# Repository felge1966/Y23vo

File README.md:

# Y23vo
Neudesign des Mikrocomputers M.Kramer

Bisher sind folgende Baugruppen realisiert:
- CPU mit RAM und EPROM 
- BWS mit 2K Zeichengenerator 
- Floppycontroller mit u8272 (nach FA 07/1990)
- Grafikdisplaycontroller mit U82720 (nach FA 07/1990)
- 2PIO
- SIO mit U856, U857 und 8251
- Backplane mit 8 Steckplätzen

Alle Baugruppen können mit EFS 29 (A-B oder A-C) Steckverbindern oder alternativ mit DIN 41612 C 2*32 bestückt werden.

Bei CPU, 2PIO und SIO sind GALs als Decoder in Verwendung. 
Die Erstellung erfoolgte mit WinCUPL. Die Sourcen liegen im Verzeichnis

Die Verzeichnisse Redesign 2020 und Redesign 2022 stammen von der Nachetwicklung im Robotrontechnik-Forum.
-> ferrytale

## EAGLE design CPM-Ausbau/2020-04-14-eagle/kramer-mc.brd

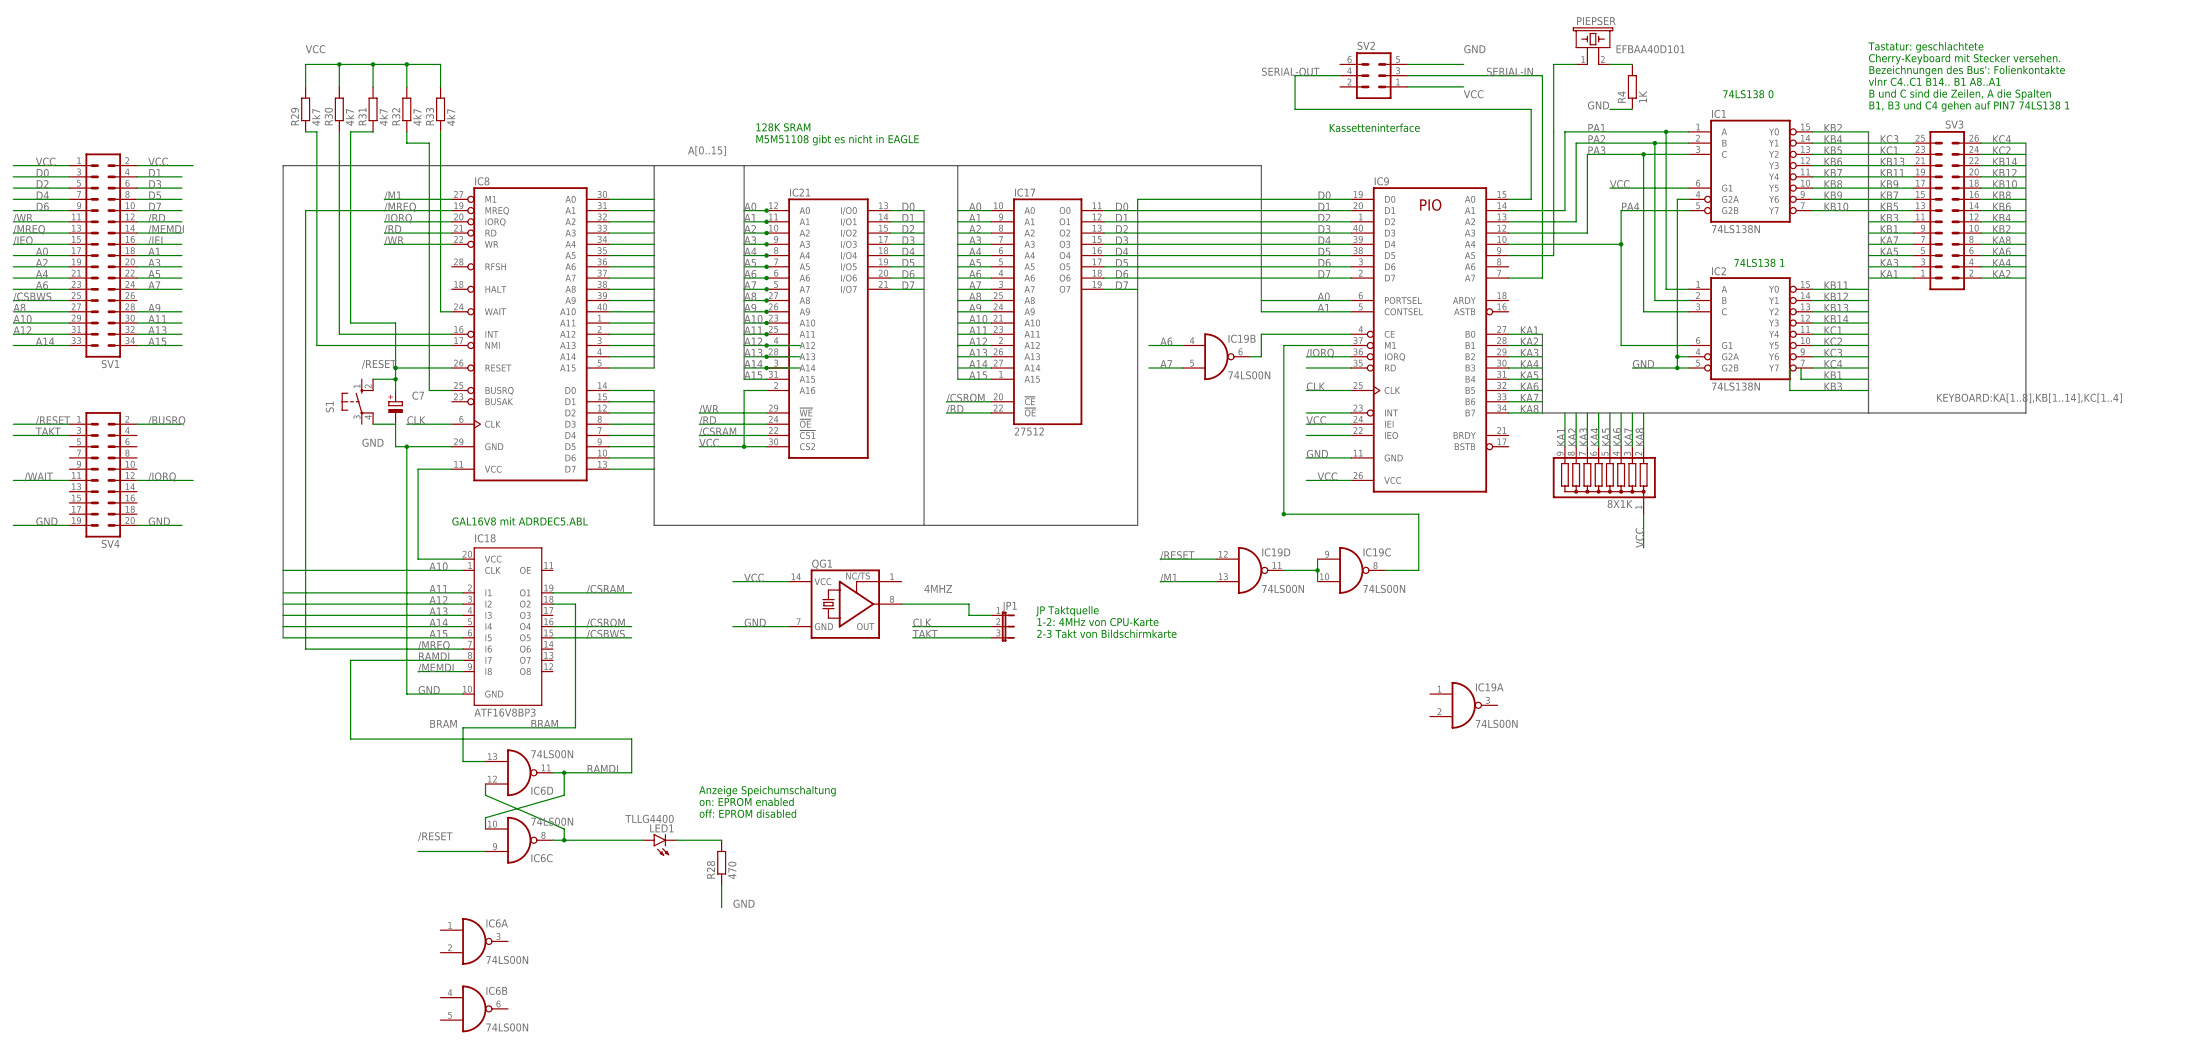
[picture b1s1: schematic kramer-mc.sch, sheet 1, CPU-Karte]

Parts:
8X1K: G08R; SIL9
C7: CPOL-EUE2-5; E2-5
IC1, IC2: 74LS138N; DIL16
IC6, IC19: 74LS00N; DIL14
IC8: Z80CPU; DIL40
IC9: Z80PIO; DIL40
IC17: 27512; DIL28
IC18: ATF16V8BP3; DIL20
IC21: LP621024CM; SOP32L
JP1: JP2E; JP2
LED1: TLLG4400; LED3MM
PIEPSER: EFBAA40D101
QG1: XO-14; DIL14S
R4: 1K; 0207/10
R28: 470; 0207/10
R29, R30, R31, R32, R33: 4k7; 0207/10
S1: 10-XX; B3F-10XX
SV1: ML34
SV2: ML6
SV3: ML26L
SV4: ML20

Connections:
4MHZ: JP1.1, QG1.8 (OUT)
/BUSRQ: SV4.2; also elsewhere on the board
/CSBWS: IC18.15 (O5), SV1.25; also elsewhere on the board
/CSRAM: IC18.19 (O1), IC21.22 (!CS1)
/CSROM: IC17.20 (!CE), IC18.16 (O4)
/IEI: SV1.16; also elsewhere on the board
/IEO: SV1.15; also elsewhere on the board
/IORQ: IC8.20 (IORQ), IC9.36 (IORQ), SV4.12; also elsewhere on the board
/M1: IC8.27 (M1), IC19.13 (I1); also elsewhere on the board
/MEMDI: IC18.9 (I8), SV1.14; also elsewhere on the board
/MREQ: IC8.19 (MREQ), IC18.7 (I6), SV1.13; also elsewhere on the board
/RD: IC8.21 (RD), IC17.22 (!OE), IC21.24 (!OE), SV1.12; also elsewhere on the board
/RESET: C7.+, IC6.9 (I0), IC8.26 (RESET), IC19.12 (I0), R31.1, S1.2 (S1), SV4.1; also elsewhere on the board
/WAIT: SV4.11; also elsewhere on the board
/WR: IC8.22 (WR), IC21.29 (!WE), SV1.11; also elsewhere on the board
A0: IC8.30 (A0), IC9.6 (PORTSEL), IC17.10 (A0), IC21.12 (A0), SV1.17; also elsewhere on the board
A1: IC8.31 (A1), IC9.5 (CONTSEL), IC17.9 (A1), IC21.11 (A1), SV1.18; also elsewhere on the board
A2: IC8.32 (A2), IC17.8 (A2), IC21.10 (A2), SV1.19; also elsewhere on the board
A3: IC8.33 (A3), IC17.7 (A3), IC21.9 (A3), SV1.20; also elsewhere on the board
A4: IC8.34 (A4), IC17.6 (A4), IC21.8 (A4), SV1.21; also elsewhere on the board
A5: IC8.35 (A5), IC17.5 (A5), IC21.7 (A5), SV1.22; also elsewhere on the board
A6: IC8.36 (A6), IC17.4 (A6), IC19.4 (I0), IC21.6 (A6), SV1.23; also elsewhere on the board
A7: IC8.37 (A7), IC17.3 (A7), IC19.5 (I1), IC21.5 (A7), SV1.24; also elsewhere on the board
A8: IC8.38 (A8), IC17.25 (A8), IC21.27 (A8), SV1.27; also elsewhere on the board
A9: IC8.39 (A9), IC17.24 (A9), IC21.26 (A9), SV1.28; also elsewhere on the board
A10: IC8.40 (A10), IC17.21 (A10), IC18.1 (CLK), IC21.23 (A10), SV1.29; also elsewhere on the board
A11: IC8.1 (A11), IC17.23 (A11), IC18.2 (I1), IC21.25 (A11), SV1.30; also elsewhere on the board
A12: IC8.2 (A12), IC17.2 (A12), IC18.3 (I2), IC21.4 (A12), SV1.31; also elsewhere on the board
A13: IC8.3 (A13), IC17.26 (A13), IC18.4 (I3), IC21.28 (A13), SV1.32; also elsewhere on the board
A14: IC8.4 (A14), IC17.27 (A14), IC18.5 (I4), IC21.3 (A14), SV1.33; also elsewhere on the board
A15: IC8.5 (A15), IC17.1 (A15), IC18.6 (I5), IC21.31 (A15), SV1.34; also elsewhere on the board
BRAM: IC6.13 (I1), IC18.18 (O2)
CLK: IC8.6 (CLK), IC9.25 (CLK), JP1.2
D0: IC8.14 (D0), IC9.19 (D0), IC17.11 (O0), IC21.13 (I/O0), SV1.3; also elsewhere on the board
D1: IC8.15 (D1), IC9.20 (D1), IC17.12 (O1), IC21.14 (I/O1), SV1.4; also elsewhere on the board
D2: IC8.12 (D2), IC9.1 (D2), IC17.13 (O2), IC21.15 (I/O2), SV1.5; also elsewhere on the board
D3: IC8.8 (D3), IC9.40 (D3), IC17.15 (O3), IC21.17 (I/O3), SV1.6; also elsewhere on the board
D4: IC8.7 (D4), IC9.39 (D4), IC17.16 (O4), IC21.18 (I/O4), SV1.7; also elsewhere on the board
D5: IC8.9 (D5), IC9.38 (D5), IC17.17 (O5), IC21.19 (I/O5), SV1.8; also elsewhere on the board
D6: IC8.10 (D6), IC9.3 (D6), IC17.18 (O6), IC21.20 (I/O6), SV1.9; also elsewhere on the board
D7: IC8.13 (D7), IC9.2 (D7), IC17.19 (O7), IC21.21 (I/O7), SV1.10; also elsewhere on the board
GND: C7.-, IC1.4 (G2A), IC1.8 (GND), IC2.4 (G2A), IC2.5 (G2B), IC2.8 (GND), IC6.7 (GND), IC8.29 (GND), IC9.11 (GND), IC17.14 (GND), IC18.10 (GND), IC19.7 (GND), IC21.16 (GND), QG1.7 (GND), R4.1, R28.1, S1.4 (P1), SV2.5, SV4.19, SV4.20; also elsewhere on the board
KA1: 8X1K.9, IC9.27 (B0), SV3.1
KA2: 8X1K.8, IC9.28 (B1), SV3.2
KA3: 8X1K.7, IC9.29 (B2), SV3.3
KA4: 8X1K.6, IC9.30 (B3), SV3.4
KA5: 8X1K.5, IC9.31 (B4), SV3.5
KA6: 8X1K.4, IC9.32 (B5), SV3.6
KA7: 8X1K.3, IC9.33 (B6), SV3.7
KA8: 8X1K.2, IC9.34 (B7), SV3.8
KB1: SV3.9
KB2: IC1.15 (Y0), SV3.10
KB3: SV3.11
KB4: IC1.14 (Y1), SV3.12
KB5: IC1.13 (Y2), SV3.13
KB6: IC1.12 (Y3), SV3.14
KB7: IC1.11 (Y4), SV3.15
KB8: IC1.10 (Y5), SV3.16
KB9: IC1.9 (Y6), SV3.17
KB10: IC1.7 (Y7), SV3.18
KB11: IC2.15 (Y0), SV3.19
KB12: IC2.14 (Y1), SV3.20
KB13: IC2.13 (Y2), SV3.21
KB14: IC2.12 (Y3), SV3.22
KC1: IC2.11 (Y4), SV3.23
KC2: IC2.10 (Y5), SV3.24
KC3: IC2.9 (Y6), SV3.25
KC4: IC2.7 (Y7), SV3.26
unnamed: IC19.9 (I0), IC19.10 (I1), IC19.11 (O)
unnamed: IC8.11 (VCC), IC18.20 (VCC)
unnamed: IC6.8 (O), IC6.12 (I0), LED1.A
unnamed: LED1.K (C), R28.2
unnamed: IC9.9 (A5), PIEPSER.1
unnamed: PIEPSER.2, R4.2
unnamed: IC9.4 (CE), IC19.6 (O)
unnamed: IC9.37 (M1), IC19.8 (O)
unnamed: IC8.17 (NMI), R29.1
unnamed: IC8.16 (INT), R30.1
unnamed: IC8.24 (WAIT), R33.1
unnamed: IC8.25 (BUSRQ), R32.1
PA1: IC1.1 (A), IC2.1 (A), IC9.14 (A1)
PA2: IC1.2 (B), IC2.2 (B), IC9.13 (A2)
PA3: IC1.3 (C), IC2.3 (C), IC9.12 (A3)
PA4: IC1.5 (G2B), IC2.6 (G1), IC9.10 (A4)
RAMDI: IC6.10 (I1), IC6.11 (O), IC18.8 (I7)
SERIAL-IN: IC9.7 (A7), SV2.3
SERIAL-OUT: IC9.15 (A0), SV2.4
TAKT: JP1.3, SV4.3; also elsewhere on the board
VCC: 8X1K.1, IC1.6 (G1), IC1.16 (VCC), IC2.16 (VCC), IC6.14 (VCC), IC9.24 (IEI), IC9.26 (VCC), IC17.28 (VCC), IC19.14 (VCC), IC21.2 (A16), IC21.30 (CS2), IC21.32 (VCC), QG1.14 (VCC), R29.2, R30.2, R31.2, R32.2, R33.2, SV1.1, SV1.2, SV2.1; also elsewhere on the board

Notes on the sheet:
GAL16V8 mit ADRDEC5.ABL
Tastatur: geschlachtete Cherry-Keyboard mit Stecker versehen. Bezeichnungen des Bus': Folienkontakte vlnr C4..C1 B14.. B1 A8..A1 B und C sind die Zeilen, A die Spalten B1, B3 und C4 gehen auf PIN7 74LS138 1
74LS138 1
74LS138 0
Kassetteninterface
128K SRAM M5M51108 gibt es nicht in EAGLE
Anzeige Speichumschaltung on: EPROM enabled off: EPROM disabled
JP Taktquelle 1-2: 4MHz von CPU-Karte 2-3 Takt von Bildschirmkarte

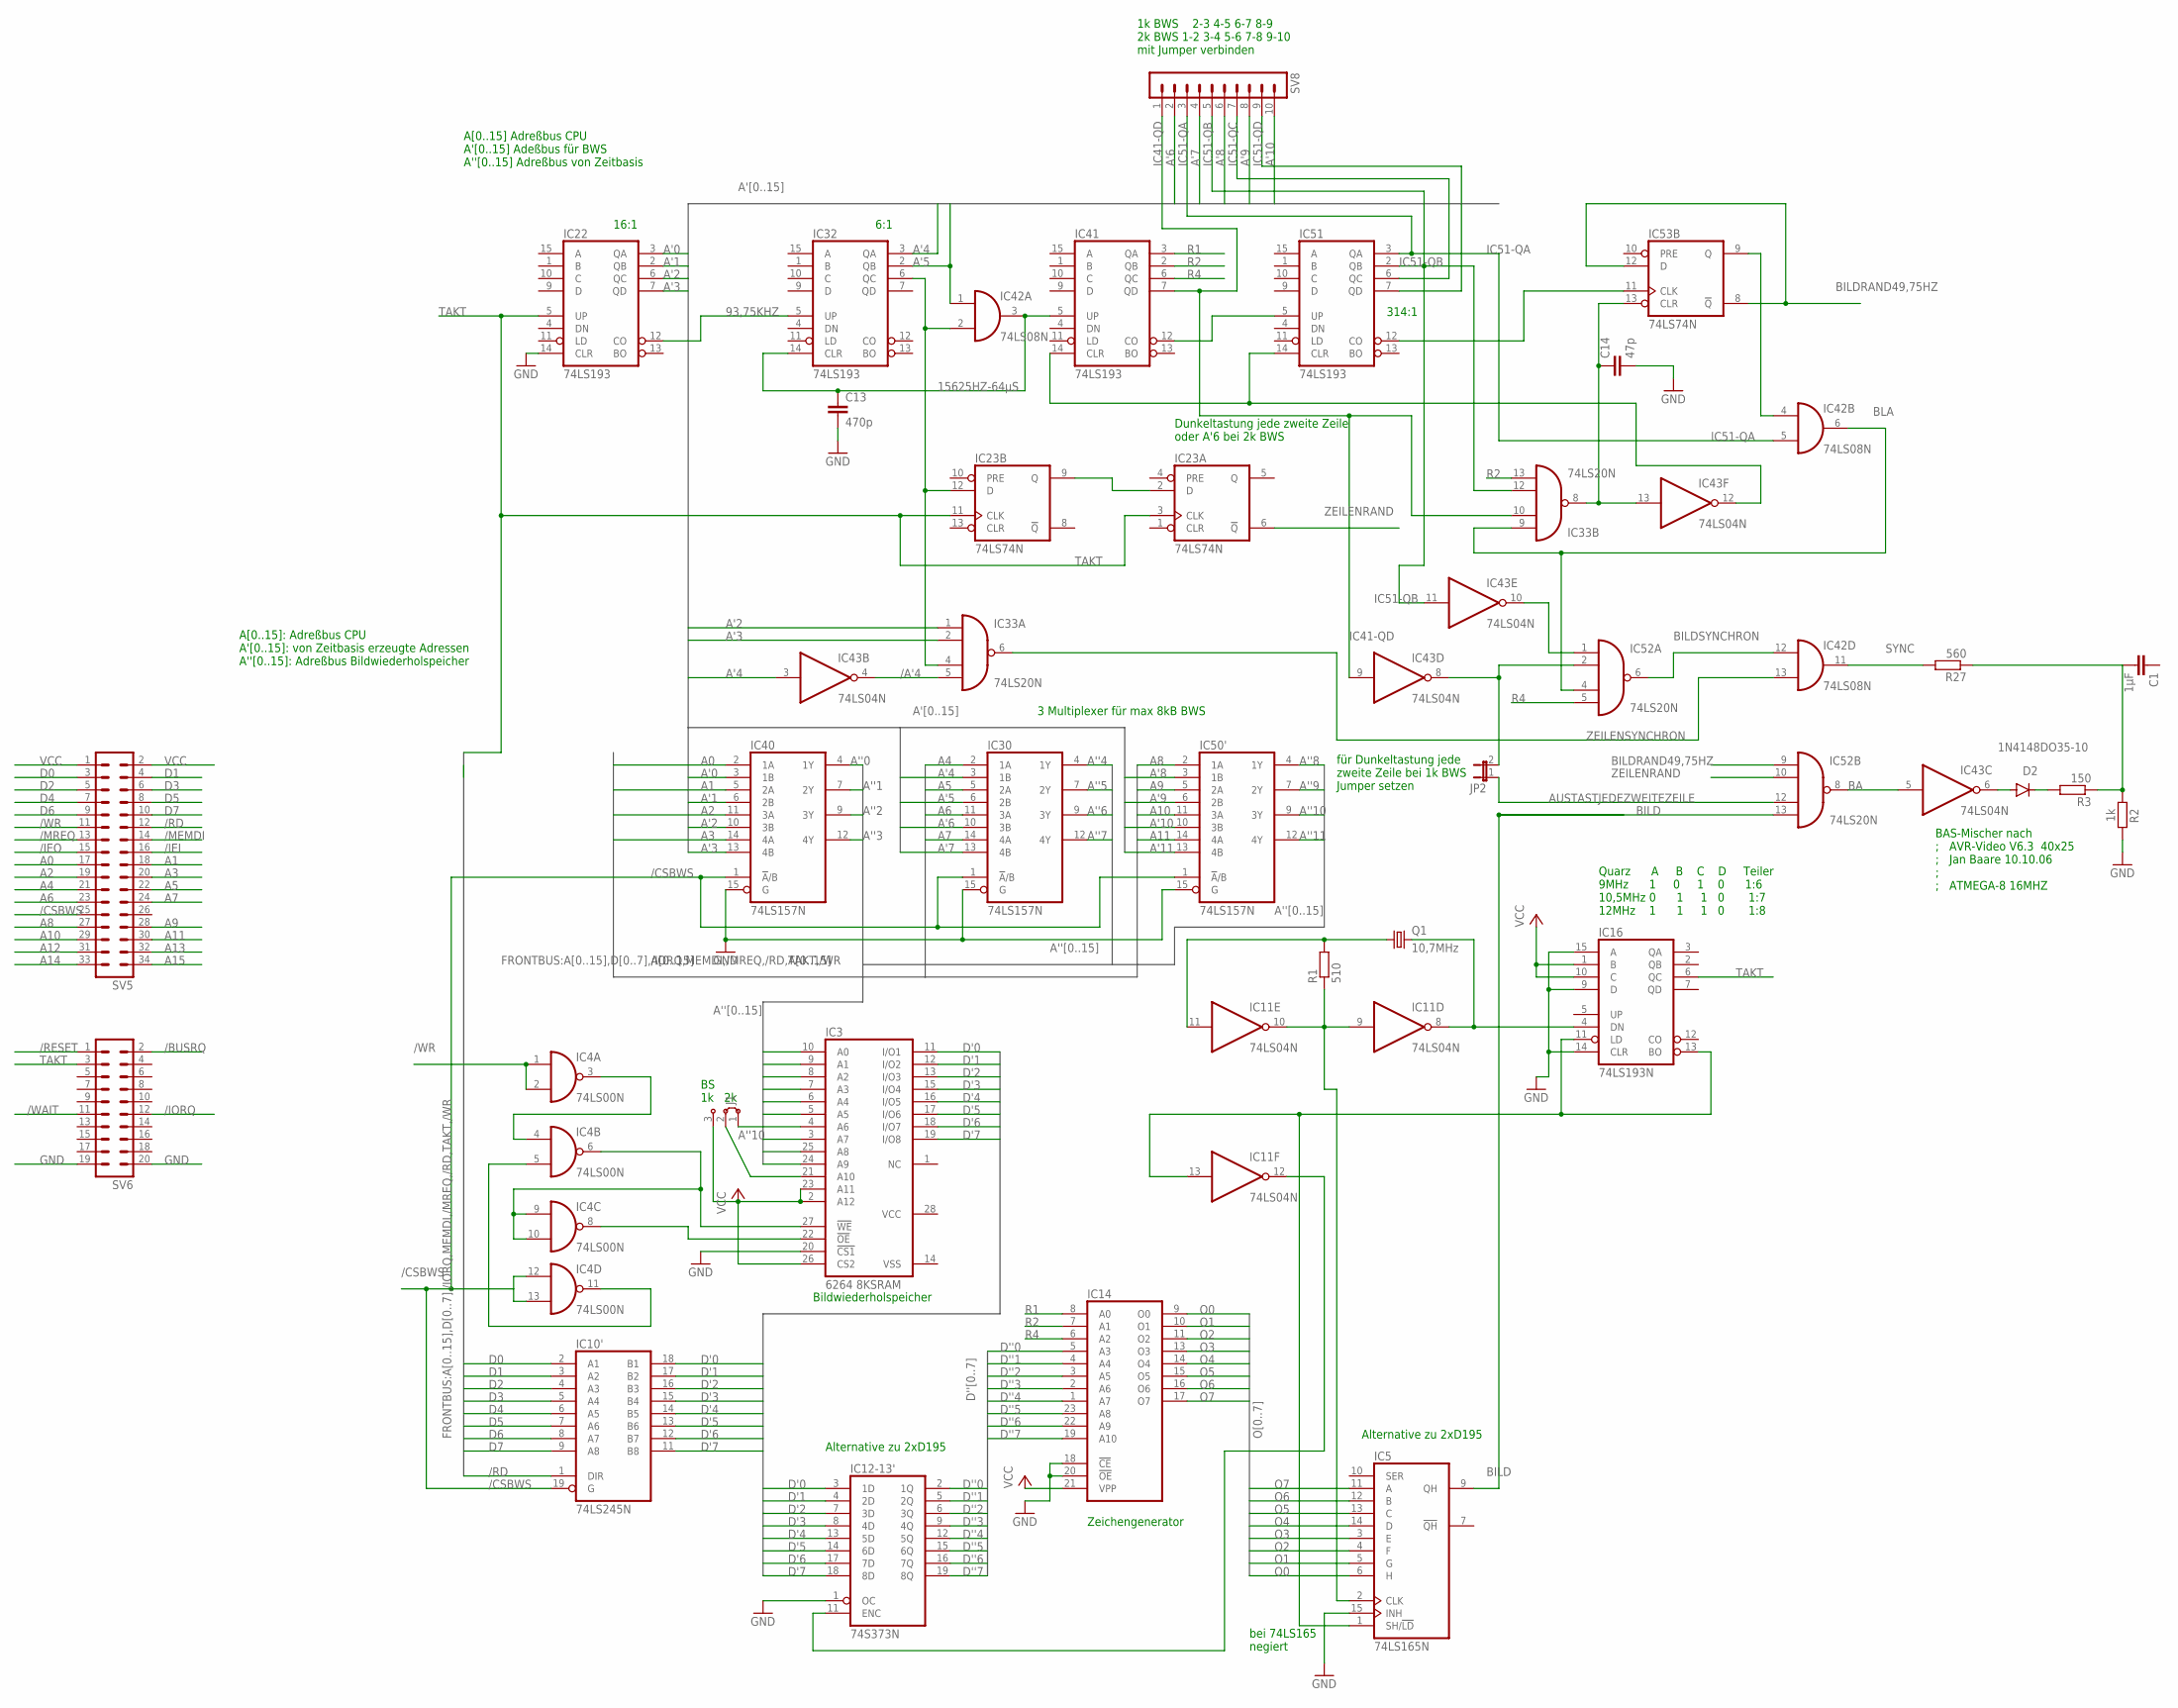
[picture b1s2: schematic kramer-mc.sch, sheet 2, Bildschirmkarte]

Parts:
C1: 1µF; C050-025X075
C13: 470p; C050-024X044
C14: 47p; C050-024X044
D2: 1N4148DO35-10; DO35-10
IC3: 6264 8KSRAM; DIL28-6
IC4: 74LS00N; DIL14
IC5: 74LS165N; DIL16
IC10': 74LS245N; DIL20
IC11, IC43: 74LS04N; DIL14
IC12-13': 74S373N; DIL20
IC14: 2716; DIL24
IC16: 74LS193N; DIL16
IC22, IC32, IC41, IC51: 74LS193; DIL16
IC23, IC53: 74LS74N; DIL14
IC30, IC40, IC50': 74LS157N; DIL16
IC33, IC52: 74LS20N; DIL14
IC42: 74LS08N; DIL14
J1: J2X2MM; 04C
JP2: JP1E; JP1
Q1: 10,7MHz; HC49U-V
R1: 510; 0309/12
R2: 1k; 0309/12
R3: 150; 0309/12
R27: 560; 0309/12
SV5: ML34
SV6: ML20
SV8: MA10-1

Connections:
93,75KHZ: IC22.12 (CO), IC32.5 (UP)
15625HZ-64µS: C13.1, IC32.14 (CLR), IC41.5 (UP), IC42.3 (O)
/A'4: IC33.5 (I3), IC43.4 (O)
/BUSRQ: SV6.2; also elsewhere on the board
/CSBWS: IC4.12 (I0), IC4.13 (I1), IC10'.19 (G), IC30.1 (!A!/B), IC40.1 (!A!/B), IC50'.1 (!A!/B), SV5.25; also elsewhere on the board
/IEI: SV5.16; also elsewhere on the board
/IEO: SV5.15; also elsewhere on the board
/IORQ: SV6.12; also elsewhere on the board
/MEMDI: SV5.14; also elsewhere on the board
/MREQ: SV5.13; also elsewhere on the board
/RD: IC10'.1 (DIR), SV5.12; also elsewhere on the board
/RESET: SV6.1; also elsewhere on the board
/WAIT: SV6.11; also elsewhere on the board
/WR: IC4.1 (I0), IC4.2 (I1), SV5.11; also elsewhere on the board
A0: IC40.2 (1A), SV5.17; also elsewhere on the board
A1: IC40.5 (2A), SV5.18; also elsewhere on the board
A2: IC40.11 (3A), SV5.19; also elsewhere on the board
A3: IC40.14 (4A), SV5.20; also elsewhere on the board
A4: IC30.2 (1A), SV5.21; also elsewhere on the board
A5: IC30.5 (2A), SV5.22; also elsewhere on the board
A6: IC30.11 (3A), SV5.23; also elsewhere on the board
A7: IC30.14 (4A), SV5.24; also elsewhere on the board
A8: IC50'.2 (1A), SV5.27; also elsewhere on the board
A9: IC50'.5 (2A), SV5.28; also elsewhere on the board
A10: IC50'.11 (3A), SV5.29; also elsewhere on the board
A11: IC50'.14 (4A), SV5.30; also elsewhere on the board
A12: SV5.31; also elsewhere on the board
A13: SV5.32; also elsewhere on the board
A14: SV5.33; also elsewhere on the board
A15: SV5.34; also elsewhere on the board
A'0: IC22.3 (QA), IC40.3 (1B)
A'1: IC22.2 (QB), IC40.6 (2B)
A'2: IC22.6 (QC), IC33.1 (I0), IC40.10 (3B)
A'3: IC22.7 (QD), IC33.2 (I1), IC40.13 (4B)
A'4: IC30.3 (1B), IC32.3 (QA), IC43.3 (I)
A'5: IC30.6 (2B), IC32.2 (QB), IC42.1 (I0)
A'6: IC30.10 (3B), SV8.2
A'7: IC30.13 (4B), SV8.4
A'8: IC50'.3 (1B), SV8.6
A'9: IC50'.6 (2B), SV8.8
A'10: IC50'.10 (3B), SV8.10
A'11: IC50'.13 (4B)
A''0: IC3.10 (A0), IC40.4 (1Y)
A''1: IC3.9 (A1), IC40.7 (2Y)
A''2: IC3.8 (A2), IC40.9 (3Y)
A''3: IC3.7 (A3), IC40.12 (4Y)
A''4: IC3.6 (A4), IC30.4 (1Y)
A''5: IC3.5 (A5), IC30.7 (2Y)
A''6: IC3.4 (A6), IC30.9 (3Y)
A''7: IC3.3 (A7), IC30.12 (4Y)
A''8: IC3.25 (A8), IC50'.4 (1Y)
A''9: IC3.24 (A9), IC50'.7 (2Y)
A''10: IC50'.9 (3Y), J1.1
A''11: IC50'.12 (4Y)
AUSTASTJEDEZWEITEZEILE: IC52.12 (I2), JP2.1
BA: IC43.5 (I), IC52.8 (O)
BILD: IC5.9 (QH), IC52.13 (I3)
BILDRAND49,75HZ: IC52.9 (I0), IC53.8 (!Q), IC53.12 (D)
BILDSYNCHRON: IC42.12 (I0), IC52.6 (O)
BLA: IC33.9 (I0), IC42.6 (O), IC52.4 (I2)
D0: IC10'.2 (A1), SV5.3; also elsewhere on the board
D1: IC10'.3 (A2), SV5.4; also elsewhere on the board
D2: IC10'.4 (A3), SV5.5; also elsewhere on the board
D3: IC10'.5 (A4), SV5.6; also elsewhere on the board
D4: IC10'.6 (A5), SV5.7; also elsewhere on the board
D5: IC10'.7 (A6), SV5.8; also elsewhere on the board
D6: IC10'.8 (A7), SV5.9; also elsewhere on the board
D7: IC10'.9 (A8), SV5.10; also elsewhere on the board
D'0: IC3.11 (I/O1), IC10'.18 (B1), IC12-13'.3 (1D)
D'1: IC3.12 (I/O2), IC10'.17 (B2), IC12-13'.4 (2D)
D'2: IC3.13 (I/O3), IC10'.16 (B3), IC12-13'.7 (3D)
D'3: IC3.15 (I/O4), IC10'.15 (B4), IC12-13'.8 (4D)
D'4: IC3.16 (I/O5), IC10'.14 (B5), IC12-13'.13 (5D)
D'5: IC3.17 (I/O6), IC10'.13 (B6), IC12-13'.14 (6D)
D'6: IC3.18 (I/O7), IC10'.12 (B7), IC12-13'.17 (7D)
D'7: IC3.19 (I/O8), IC10'.11 (B8), IC12-13'.18 (8D)
D''0: IC12-13'.2 (1Q), IC14.5 (A3)
D''1: IC12-13'.5 (2Q), IC14.4 (A4)
D''2: IC12-13'.6 (3Q), IC14.3 (A5)
D''3: IC12-13'.9 (4Q), IC14.2 (A6)
D''4: IC12-13'.12 (5Q), IC14.1 (A7)
D''5: IC12-13'.15 (6Q), IC14.23 (A8)
D''6: IC12-13'.16 (7Q), IC14.22 (A9)
D''7: IC12-13'.19 (8Q), IC14.19 (A10)
GND: C13.2, C14.2, IC3.20 (!CS1), IC4.7 (GND), IC5.8 (GND), IC5.15 (INH), IC10'.10 (GND), IC11.7 (GND), IC12-13'.1 (OC), IC12-13'.10 (GND), IC14.12 (GND), IC14.18 (!CE), IC14.20 (!OE), IC16.8 (GND), IC16.9 (D), IC16.14 (CLR), IC16.15 (A), IC22.8 (GND), IC22.14 (CLR), IC23.7 (GND), IC30.8 (GND), IC30.15 (G), IC32.8 (GND), IC33.7 (GND), IC40.8 (GND), IC40.15 (G), IC41.8 (GND), IC42.7 (GND), IC43.7 (GND), IC50'.8 (GND), IC50'.15 (G), IC51.8 (GND), IC52.7 (GND), IC53.7 (GND), R2.2, SV6.19, SV6.20; also elsewhere on the board
IC41-QD: IC33.10 (I1), IC41.7 (QD), IC43.9 (I), SV8.1
IC51-QA: IC42.5 (I1), IC51.3 (QA), SV8.3
IC51-QB: IC33.12 (I2), IC43.11 (I), IC51.2 (QB), SV8.5
IC51-QC: IC51.6 (QC), SV8.7
IC51-QD: IC51.7 (QD), SV8.9
unnamed: IC43.8 (O), IC52.2 (I1), JP2.2
unnamed: IC41.12 (CO), IC51.5 (UP)
unnamed: IC23.12 (D), IC32.6 (QC), IC33.4 (I2), IC42.2 (I1)
unnamed: IC23.2 (D), IC23.9 (Q)
unnamed: IC41.14 (CLR), IC43.12 (O), IC51.14 (CLR)
unnamed: IC51.12 (CO), IC53.11 (CLK)
unnamed: IC3.21 (A10), J1.2
unnamed: IC42.4 (I0), IC53.9 (Q)
unnamed: IC4.3 (O), IC4.4 (I0)
unnamed: C14.1, IC33.8 (O), IC43.13 (I), IC53.13 (CLR)
unnamed: IC43.10 (O), IC52.1 (I0)
unnamed: IC5.2 (CLK), IC11.9 (I), IC11.10 (O), R1.1
unnamed: IC11.12 (O), IC12-13'.11 (ENC)
unnamed: D2.A, IC43.6 (O)
unnamed: IC11.8 (O), IC16.4 (DN), Q1.2
unnamed: IC11.11 (I), Q1.1, R1.2
unnamed: IC5.1 (SH/!LD), IC11.13 (I), IC16.11 (LD), IC16.13 (BO)
unnamed: D2.C, R3.2
unnamed: C1.2, R2.1, R3.1, R27.1
unnamed: IC4.5 (I1), IC4.11 (O)
unnamed: IC3.22 (!OE), IC4.8 (O)
unnamed: IC3.27 (!WE), IC4.6 (O), IC4.9 (I0), IC4.10 (I1)
O0: IC5.6 (H), IC14.9 (O0)
O1: IC5.5 (G), IC14.10 (O1)
O2: IC5.4 (F), IC14.11 (O2)
O3: IC5.3 (E), IC14.13 (O3)
O4: IC5.14 (D), IC14.14 (O4)
O5: IC5.13 (C), IC14.15 (O5)
O6: IC5.12 (B), IC14.16 (O6)
O7: IC5.11 (A), IC14.17 (O7)
R1: IC14.8 (A0), IC41.3 (QA)
R2: IC14.7 (A1), IC33.13 (I3), IC41.2 (QB)
R4: IC14.6 (A2), IC41.6 (QC), IC52.5 (I3)
SYNC: IC42.11 (O), R27.2
TAKT: IC16.6 (QC), IC22.5 (UP), IC23.3 (CLK), IC23.11 (CLK), SV6.3; also elsewhere on the board
VCC: IC3.2 (A12), IC3.23 (A11), IC3.26 (CS2), IC3.28 (VCC), IC4.14 (VCC), IC5.16 (VCC), IC10'.20 (VCC), IC11.14 (VCC), IC12-13'.20 (VCC), IC14.21 (VPP), IC14.24 (VCC), IC16.1 (B), IC16.10 (C), IC16.16 (VCC), IC22.16 (VCC), IC23.14 (VCC), IC30.16 (VCC), IC32.16 (VCC), IC33.14 (VCC), IC40.16 (VCC), IC41.16 (VCC), IC42.14 (VCC), IC43.14 (VCC), IC50'.16 (VCC), IC51.16 (VCC), IC52.14 (VCC), IC53.14 (VCC), J1.3, SV5.1, SV5.2; also elsewhere on the board
VSS: IC3.14 (VSS)
ZEILENRAND: IC23.6 (!Q), IC52.10 (I1)
ZEILENSYNCHRON: IC33.6 (O), IC42.13 (I1)

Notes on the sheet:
Alternative zu 2xD195
bei 74LS165 negiert
A[0..15] Adreßbus CPU A'[0..15] Adeßbus für BWS A''[0..15] Adreßbus von Zeitbasis
Bildwiederholspeicher
Zeichengenerator
3 Multiplexer für max 8kB BWS
Quarz A B C D Teiler 9MHz 1 0 1 0 1:6 10,5MHz 0 1 1 0 1:7 12MHz 1 1 1 0 1:8
BAS-Mischer nach ; AVR-Video V6.3 40x25 ; Jan Baare 10.10.06 ; ; ATMEGA-8 16MHZ
A[0..15]: Adreßbus CPU A'[0..15]: von Zeitbasis erzeugte Adressen A''[0..15]: Adreßbus Bildwiederholspeicher
Dunkeltastung jede zweite Zeile oder A'6 bei 2k BWS
16:1
6:1
für Dunkeltastung jede zweite Zeile bei 1k BWS Jumper setzen
BS 1k 2k
1k BWS 2-3 4-5 6-7 8-9 2k BWS 1-2 3-4 5-6 7-8 9-10 mit Jumper verbinden
314:1

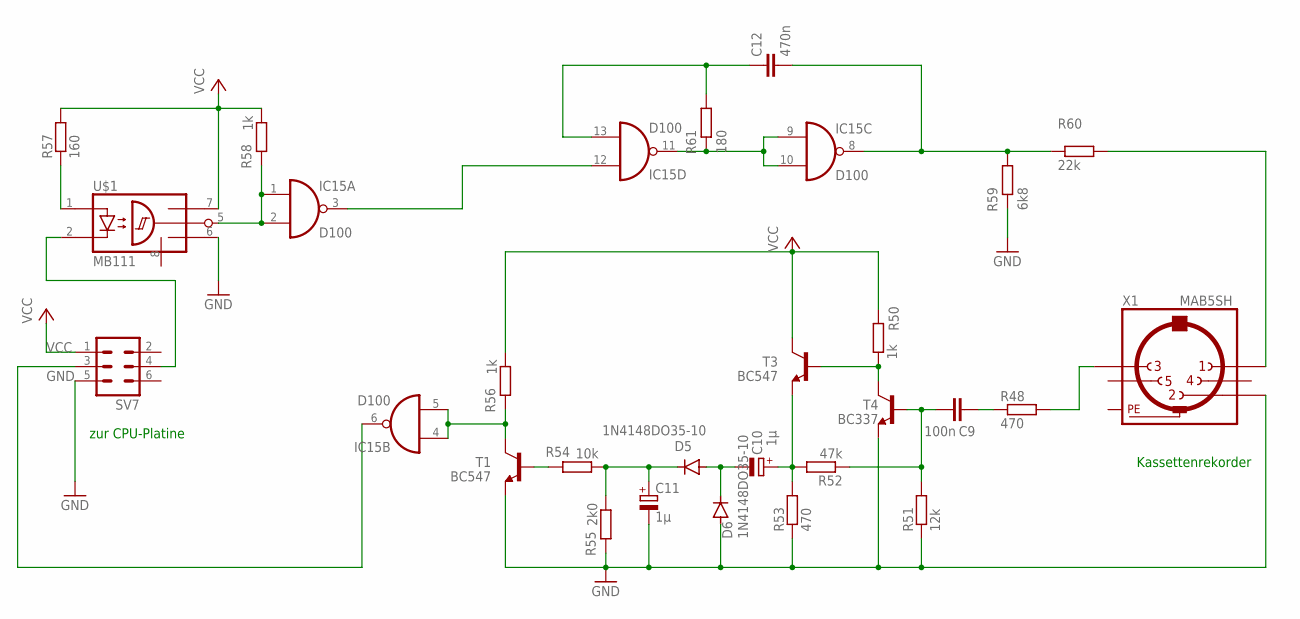
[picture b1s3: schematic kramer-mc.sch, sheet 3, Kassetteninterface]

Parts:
C9: 100n; C025-025X050
C10, C11: 1µ; E2,5-6E
C12: 470n; C150-064X183
D5, D6: 1N4148DO35-10; DO35-10
IC15: D100; DIL14
R48, R53: 470; 0207/10
R50, R56, R58: 1k; 0207/10
R51: 12k; 0207/10
R52: 47k; 0207/10
R54: 10k; 0207/10
R55: 2k0; 0207/10
R57: 160; 0207/10
R59: 6k8; 0207/10
R60: 22k; 0207/10
R61: 180; 0207/10
SV7: ML6
T1, T3: BC547; TO92
T4: BC337; TO92
U$1: MB111; DIL8
X1: MAB5SH

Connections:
GND: C11.-, D6.A, IC15.7 (GND), R51.1, R53.1, R55.2, R59.2, SV7.5, T1.1 (E), T4.1 (E), U$1.6 (GND1), X1.2; also elsewhere on the board
unnamed: IC15.6 (O), SV7.3
unnamed: SV7.4, U$1.2 (C)
unnamed: R48.2, X1.3
unnamed: C9.1, R48.1
unnamed: C9.2, R51.2, R52.1, T4.2 (B)
unnamed: R50.1, T3.2 (B), T4.3 (C)
unnamed: R57.1, U$1.1 (A)
unnamed: C10.+, R52.2, R53.2, T3.1 (E)
unnamed: IC15.1 (I0), IC15.2 (I1), R58.2, U$1.5 (OUT1)
unnamed: C10.-, D5.A, D6.C
unnamed: C11.+, D5.C, R54.1, R55.1
unnamed: R60.2, X1.1
unnamed: R54.2, T1.2 (B)
unnamed: IC15.4 (I0), IC15.5 (I1), R56.2, T1.3 (C)
unnamed: IC15.9 (I0), IC15.10 (I1), IC15.11 (O), R61.2
unnamed: C12.1, IC15.13 (I1), R61.1
unnamed: C12.2, IC15.8 (O), R59.1, R60.1
unnamed: IC15.3 (O), IC15.12 (I0)
PE: X1.PE, X1.PE@ (PE)
VCC: IC15.14 (VCC), R50.2, R56.1, R57.2, R58.1, SV7.1, T3.3 (C), U$1.7 (VCC1); also elsewhere on the board

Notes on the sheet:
zur CPU-Platine
Kassettenrekorder

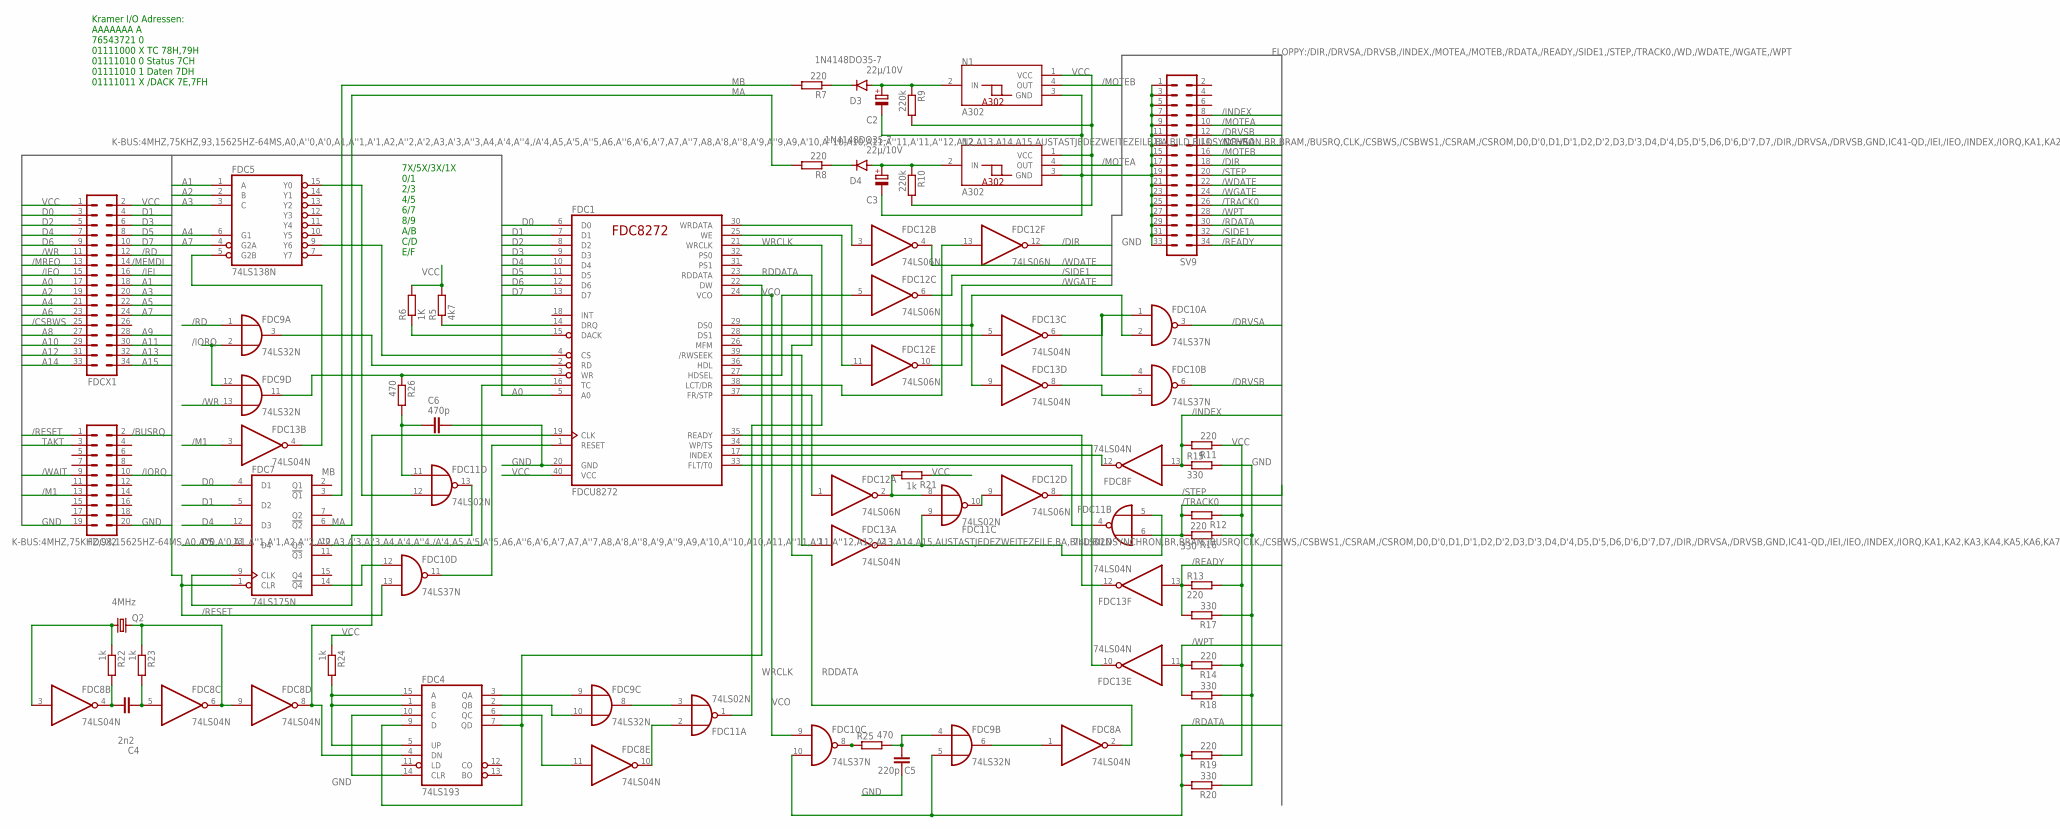
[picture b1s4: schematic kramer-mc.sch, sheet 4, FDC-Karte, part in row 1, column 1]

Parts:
C2, C3: 22µ/10V; E2,5-5
C4: 2n2; C025-025X050
C5: 220p; C025-025X050
C6: 470p; C025-025X050
D3, D4: 1N4148DO35-7; DO35-7
FDC1: FDCU8272; DIL40
FDC4: 74LS193; DIL16
FDC5: 74LS138N; DIL16
FDC7: 74LS175N; DIL16
FDC8, FDC13: 74LS04N; DIL14
FDC9: 74LS32N; DIL14
FDC10: 74LS37N; DIL14
FDC11: 74LS02N; DIL14
FDC12: 74LS06N; DIL14
FDCX1: ML34
FDCX2: ML20
N1, N2: A302; DIL04
Q2: 4MHz; HC49U-V
R5: 4k7; 0207/10
R6: 1K; 0207/10
R7, R8, R11, R12, R13, R14, R19: 220; 0207/10
R9, R10: 220k; 0207/10
R15, R16, R17, R18, R20: 330; 0207/10
R21, R22, R23, R24: 1k; 0207/10
R25, R26: 470; 0207/10
SV9: ML34

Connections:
/BUSRQ: FDCX2.2; also elsewhere on the board
/CSBWS: FDCX1.25; also elsewhere on the board
/DIR: FDC12.12 (O), SV9.18
/DRVSA: FDC10.3 (O), SV9.14
/DRVSB: FDC10.6 (O), SV9.12
/IEI: FDCX1.16; also elsewhere on the board
/IEO: FDCX1.15; also elsewhere on the board
/INDEX: FDC8.13 (I), R11.2, R15.1, SV9.8
/IORQ: FDC9.2 (I1), FDC9.12 (I0), FDCX2.10; also elsewhere on the board
/M1: FDC13.3 (I), FDCX2.13; also elsewhere on the board
/MEMDI: FDCX1.14; also elsewhere on the board
/MOTEA: N2.4 (OUT), SV9.10
/MOTEB: N1.4 (OUT), SV9.16
/MREQ: FDCX1.13; also elsewhere on the board
/RD: FDC9.1 (I0), FDCX1.12; also elsewhere on the board
/RDATA: FDC9.5 (I1), FDC10.10 (I1), R19.2, R20.2, SV9.30
/READY: FDC13.13 (I), R13.1, R17.2, SV9.34
/RESET: FDC7.1 (CLR), FDC10.13 (I1), FDCX2.1; also elsewhere on the board
/SIDE1: FDC12.6 (O), SV9.32
/STEP: FDC12.8 (O), SV9.20
/TRACK0: FDC11.6 (I1), R12.2, R16.2, SV9.26
/WAIT: FDCX2.9; also elsewhere on the board
/WDATE: FDC12.4 (O), SV9.22
/WGATE: FDC12.10 (O), SV9.24
/WPT: FDC13.11 (I), R14.2, R18.2, SV9.28
/WR: FDC9.13 (I1), FDCX1.11; also elsewhere on the board
A0: FDC1.5 (A0), FDCX1.17; also elsewhere on the board
A1: FDC5.1 (A), FDCX1.18; also elsewhere on the board
A2: FDC5.2 (B), FDCX1.19; also elsewhere on the board
A3: FDC5.3 (C), FDCX1.20; also elsewhere on the board
A4: FDC5.6 (G1), FDCX1.21; also elsewhere on the board
A5: FDCX1.22; also elsewhere on the board
A6: FDCX1.23; also elsewhere on the board
A7: FDC5.4 (G2A), FDCX1.24; also elsewhere on the board
A8: FDCX1.27; also elsewhere on the board
A9: FDCX1.28; also elsewhere on the board
A10: FDCX1.29; also elsewhere on the board
A11: FDCX1.30; also elsewhere on the board
A12: FDCX1.31; also elsewhere on the board
A13: FDCX1.32; also elsewhere on the board
A14: FDCX1.33; also elsewhere on the board
A15: FDCX1.34; also elsewhere on the board
D0: FDC1.6 (D0), FDC7.4 (D1), FDCX1.3; also elsewhere on the board
D1: FDC1.7 (D1), FDC7.5 (D2), FDCX1.4; also elsewhere on the board
D2: FDC1.8 (D2), FDCX1.5; also elsewhere on the board
D3: FDC1.9 (D3), FDCX1.6; also elsewhere on the board
D4: FDC1.10 (D4), FDC7.12 (D3), FDCX1.7; also elsewhere on the board
D5: FDC1.11 (D5), FDC7.13 (D4), FDCX1.8; also elsewhere on the board
D6: FDC1.12 (D6), FDCX1.9; also elsewhere on the board
D7: FDC1.13 (D7), FDCX1.10; also elsewhere on the board
GND: C2.-, C3.-, C5.1, C6.2, FDC1.20 (GND), FDC4.8 (GND), FDC4.10 (C), FDC4.14 (CLR), FDC5.8 (GND), FDC7.8 (GND), FDC8.7 (GND), FDC9.7 (GND), FDC10.7 (GND), FDC11.7 (GND), FDC12.7 (GND), FDC13.7 (GND), FDCX2.19, FDCX2.20, N1.3 (GND), N2.3 (GND), R15.2, R16.1, R17.1, R18.1, R20.1, SV9.1, SV9.3, SV9.5, SV9.7, SV9.9, SV9.11, SV9.13, SV9.15, SV9.17, SV9.19, SV9.21, SV9.23, SV9.25, SV9.27, SV9.29, SV9.31, SV9.33; also elsewhere on the board
MA: FDC7.6 (!Q2), R8.2
MB: FDC7.3 (!Q1), R7.2
unnamed: FDC1.14 (DRQ), R5.1
unnamed: FDC1.2 (RD), FDC9.3 (O)
unnamed: FDC1.15 (DACK), R6.1
unnamed: FDC7.14 (!Q4), FDC10.12 (I0)
unnamed: FDC1.29 (DS0), FDC10.2 (I1), FDC13.9 (I)
unnamed: FDC1.28 (DS1), FDC13.5 (I)
unnamed: FDC10.1 (I0), FDC10.4 (I0), FDC13.6 (O)
unnamed: FDC10.5 (I1), FDC13.8 (O)
unnamed: D3.C, R7.1
unnamed: C2.+, D3.A, N1.2 (IN), R9.1
unnamed: C3.+, D4.A, N2.2 (IN), R10.1
unnamed: D4.C, R8.1
unnamed: FDC1.17 (INDEX), FDC8.12 (O)
unnamed: FDC1.33 (FLT/T0), FDC11.4 (O)
unnamed: FDC1.35 (READY), FDC13.12 (O)
unnamed: FDC1.34 (WP/TS), FDC13.10 (O)
unnamed: FDC11.10 (O), FDC12.9 (I)
unnamed: FDC11.8 (I0), FDC12.2 (O), R21.2
unnamed: FDC11.5 (I0), FDC11.9 (I1), FDC13.2 (O)
unnamed: C4.1, FDC8.4 (O), R22.2
unnamed: FDC8.3 (I), Q2.1, R22.1
unnamed: FDC8.6 (O), FDC8.9 (I), Q2.2, R23.1
unnamed: C4.2, FDC8.5 (I), R23.2
unnamed: FDC1.19 (CLK), FDC4.4 (DN), FDC8.8 (O)
unnamed: FDC4.1 (B), FDC4.5 (UP), FDC4.15 (A), R24.2
unnamed: FDC1.22 (DW), FDC4.7 (QD), FDC4.9 (D)
unnamed: FDC4.3 (QA), FDC9.9 (I0)
unnamed: FDC4.2 (QB), FDC9.10 (I1)
unnamed: FDC4.6 (QC), FDC8.11 (I)
unnamed: FDC9.8 (O), FDC11.3 (I1)
unnamed: FDC8.10 (O), FDC11.2 (I0)
unnamed: FDC8.1 (I), FDC9.6 (O)
unnamed: FDC10.8 (O), R25.1
unnamed: C5.2, FDC9.4 (I0), R25.2
unnamed: FDC1.39 (/RWSEEK), FDC13.1 (I)
unnamed: FDC1.37 (FR/STP), FDC12.1 (I)
unnamed: FDC1.30 (WRDATA), FDC12.3 (I)
unnamed: FDC1.27 (HDSEL), FDC12.5 (I)
unnamed: FDC1.25 (WE), FDC12.11 (I)
unnamed: FDC1.38 (LCT/DR), FDC12.13 (I)
unnamed: FDC1.3 (WR), FDC9.11 (O), R26.1
unnamed: FDC1.1 (RESET), FDC10.11 (O)
unnamed: FDC1.16 (TC), FDC7.10 (Q3)
unnamed: FDC7.9 (CLK), FDC11.13 (O)
unnamed: C6.1, FDC11.11 (I0), R26.2
unnamed: FDC5.5 (G2B), FDC13.4 (O)
unnamed: FDC1.4 (CS), FDC5.9 (Y6)
unnamed: FDC5.15 (Y0), FDC11.12 (I1)
RDDATA: FDC1.23 (RDDATA), FDC8.2 (O)
TAKT: FDCX2.3; also elsewhere on the board
VCC: FDC1.40 (VCC), FDC4.16 (VCC), FDC5.16 (VCC), FDC7.16 (VCC), FDC8.14 (VCC), FDC9.14 (VCC), FDC10.14 (VCC), FDC11.14 (VCC), FDC12.14 (VCC), FDC13.14 (VCC), FDCX1.1, FDCX1.2, N1.1 (VCC), N2.1 (VCC), R5.2, R6.2, R9.2, R10.2, R11.1, R12.1, R13.2, R14.1, R19.1, R21.1, R24.1; also elsewhere on the board
VCO: FDC1.24 (VCO), FDC10.9 (I0)
WRCLK: FDC1.21 (WRCLK), FDC11.1 (O)

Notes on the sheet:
Kramer I/O Adressen: AAAAAAA A 76543721 0 01111000 X TC 78H,79H 01111010 0 Status 7CH 01111010 1 Daten 7DH 01111011 X /DACK 7E,7FH
7X/5X/3X/1X 0/1 2/3 4/5 6/7 8/9 A/B C/D E/F
